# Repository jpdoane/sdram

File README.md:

# sdram

Simple Verilog controller core for the 64MB [Alliance AS4C32M16SB](docs/AS4C32M16SB.pdf) or the (pin equivalent) 32MB [Winbond W9825G6KH](docs/w9825g6kh.pdf) SDRAM modules.

Includes a [board design](board/sdram.pdf) compatible with the [ChipKit shield connector](https://digilent.com/reference/_media/reference/programmable-logic/arty-z7/arty-z7-shield.png) on the [Arty Z7-20](https://digilent.com/reference/programmable-logic/arty-z7/reference-manual)

The primary intent of this project is to support larger ROM memories for [NES fpga project](https://github.com/jpdoane/nesfpga), and that will only simple memory operations as needed by the NES core will be initially supported.

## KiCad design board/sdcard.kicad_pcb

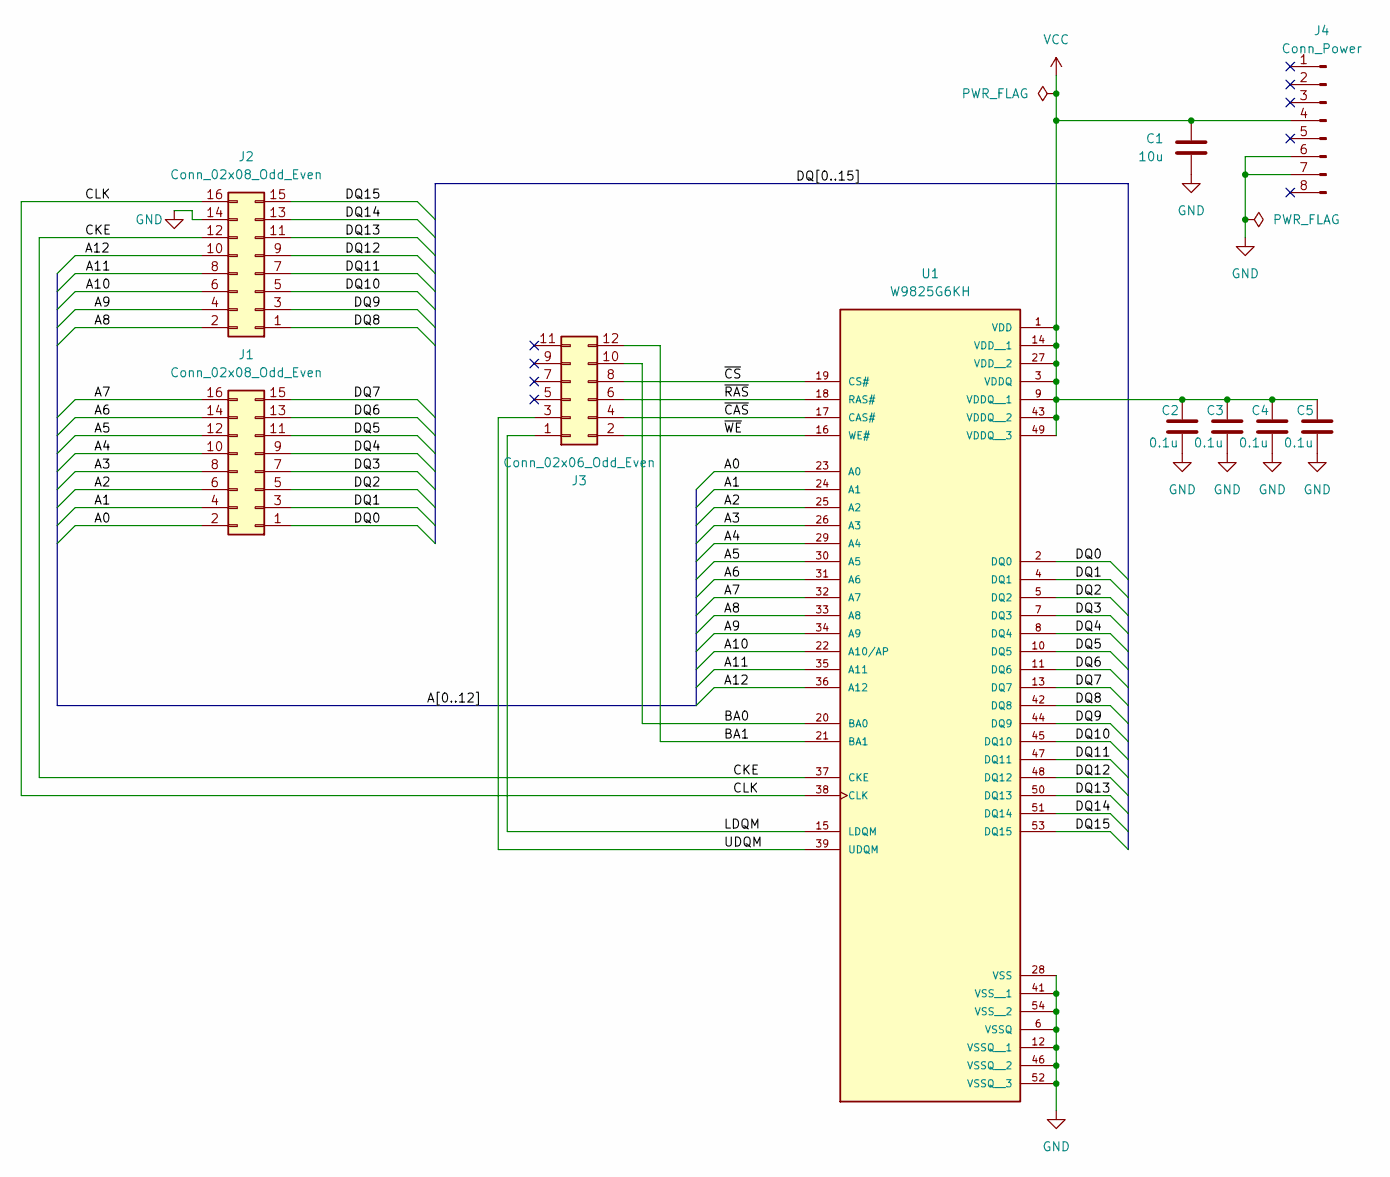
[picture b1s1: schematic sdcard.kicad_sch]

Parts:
C1: 10u; C_0805_2012Metric
C2, C3, C4, C5: 0.1u; C_0805_2012Metric
J1, J2: Conn_02x08_Odd_Even; PinHeader_2x08_P2.54mm_Vertical
J3: Conn_02x06_Odd_Even; PinHeader_2x06_P2.54mm_Vertical
J4: Conn_Power; PinHeader_1x08_P2.54mm_Vertical
U1: W9825G6KH; TSOP-II-54_22.2x10.16mm_P0.8mm; PARTREV 1.2

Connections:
/A0: J1.2, U1.23 (A0)
/A1: J1.4, U1.24 (A1)
/A2: J1.6, U1.25 (A2)
/A3: J1.8, U1.26 (A3)
/A4: J1.10, U1.29 (A4)
/A5: J1.12, U1.30 (A5)
/A6: J1.14, U1.31 (A6)
/A7: J1.16, U1.32 (A7)
/A8: J2.2, U1.33 (A8)
/A9: J2.4, U1.34 (A9)
/A10: J2.6, U1.22 (A10/AP)
/A11: J2.8, U1.35 (A11)
/A12: J2.10, U1.36 (A12)
/BA0: J3.10, U1.20 (BA0)
/BA1: J3.12, U1.21 (BA1)
/CKE: J2.12, U1.37 (CKE)
/CLK: J2.16, U1.38 (CLK)
/DQ0: J1.1, U1.2 (DQ0)
/DQ1: J1.3, U1.4 (DQ1)
/DQ2: J1.5, U1.5 (DQ2)
/DQ3: J1.7, U1.7 (DQ3)
/DQ4: J1.9, U1.8 (DQ4)
/DQ5: J1.11, U1.10 (DQ5)
/DQ6: J1.13, U1.11 (DQ6)
/DQ7: J1.15, U1.13 (DQ7)
/DQ8: J2.1, U1.42 (DQ8)
/DQ9: J2.3, U1.44 (DQ9)
/DQ10: J2.5, U1.45 (DQ10)
/DQ11: J2.7, U1.47 (DQ11)
/DQ12: J2.9, U1.48 (DQ12)
/DQ13: J2.11, U1.50 (DQ13)
/DQ14: J2.13, U1.51 (DQ14)
/DQ15: J2.15, U1.53 (DQ15)
/LDQM: J3.1, U1.15 (LDQM)
/UDQM: J3.3, U1.39 (UDQM)
/~CAS: J3.4, U1.17 (CAS#)
/~CS: J3.8, U1.19 (CS#)
/~RAS: J3.6, U1.18 (RAS#)
/~WE: J3.2, U1.16 (WE#)
GND: C1.2, C2.2, C3.2, C4.2, C5.2, J2.14, J4.6, J4.7, U1.6 (VSSQ), U1.12 (VSSQ__1), U1.28 (VSS), U1.41 (VSS__1), U1.46 (VSSQ__2), U1.52 (VSSQ__3), U1.54 (VSS__2)
VCC: C1.1, C2.1, C3.1, C4.1, C5.1, J4.4, U1.1 (VDD), U1.3 (VDDQ), U1.9 (VDDQ__1), U1.14 (VDD__1), U1.27 (VDD__2), U1.43 (VDDQ__2), U1.49 (VDDQ__3)

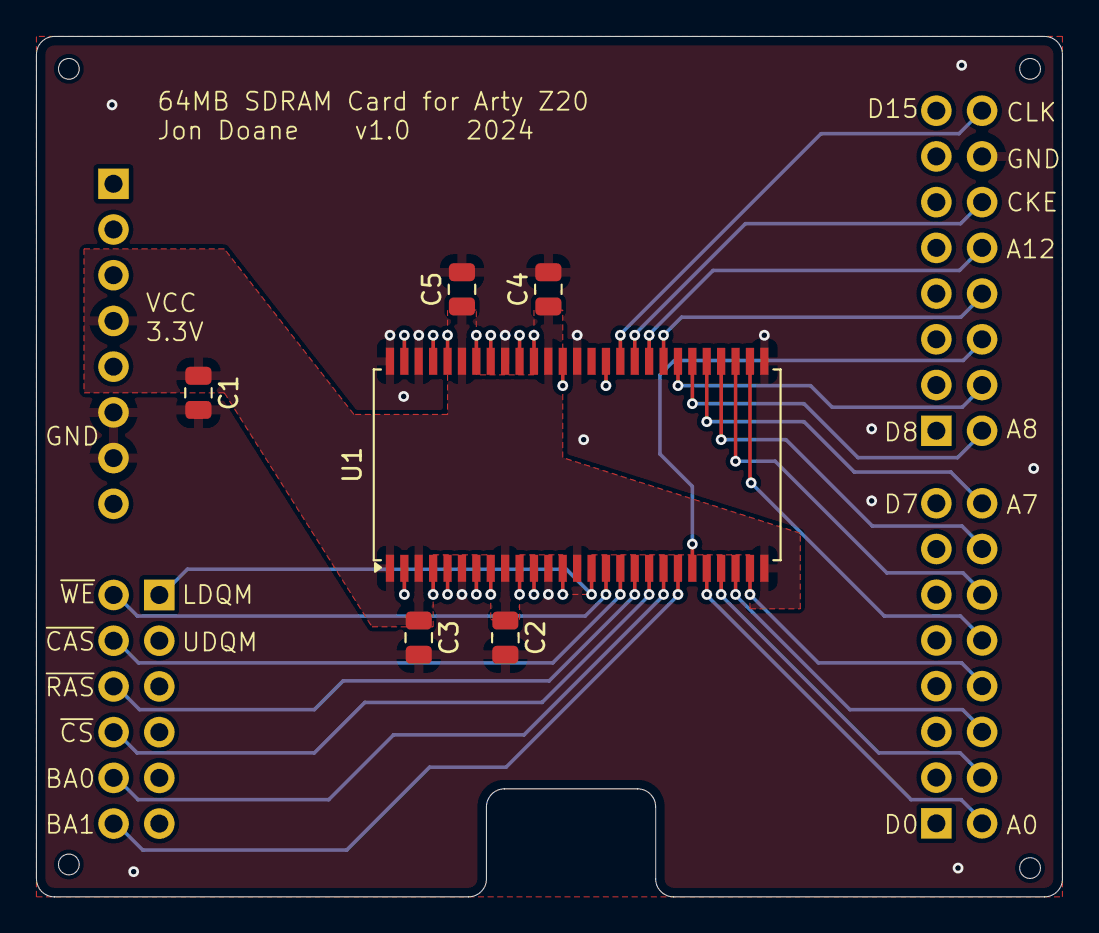
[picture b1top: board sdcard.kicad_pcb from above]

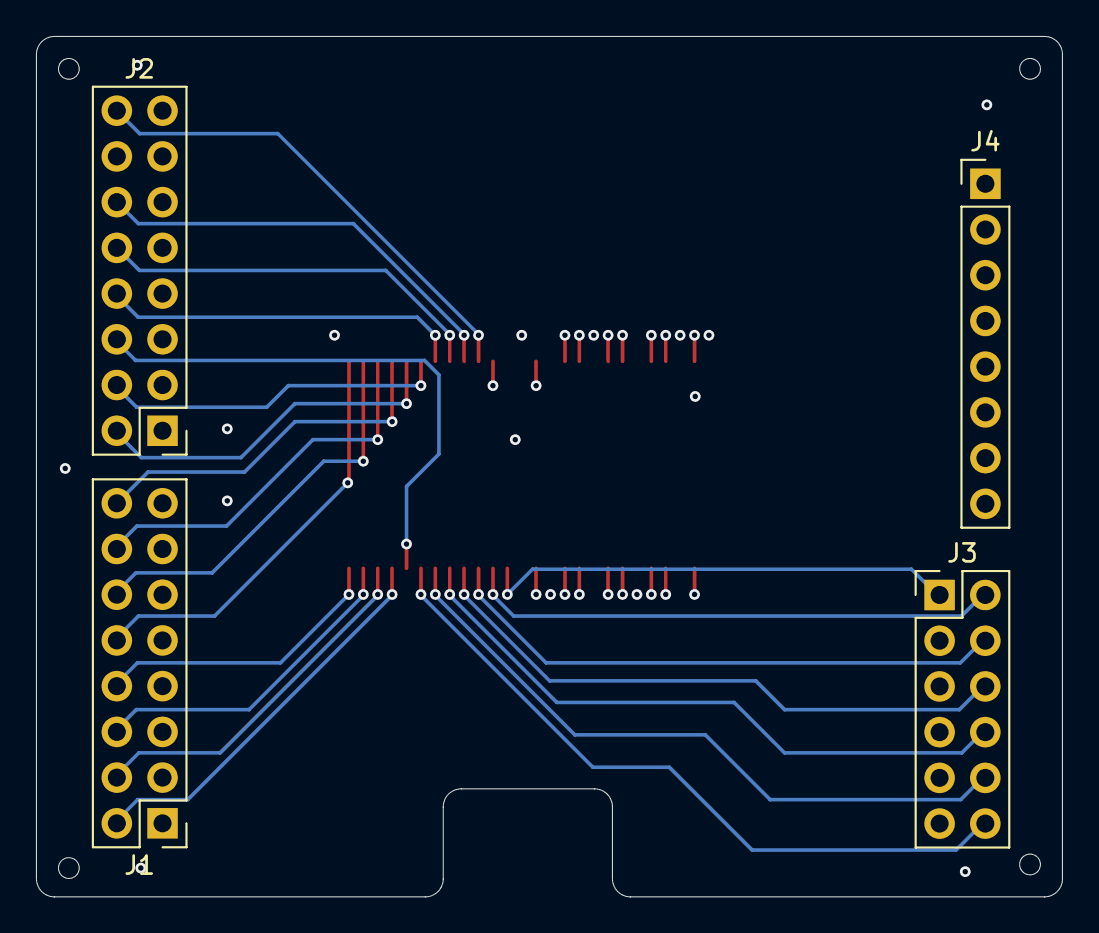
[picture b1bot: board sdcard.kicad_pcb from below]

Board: 4 copper layers, 57.0 x 47.8 mm, 10 parts (4 on the bottom side), 41 nets.

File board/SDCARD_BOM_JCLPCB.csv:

Comment,Designator,Footprint,JLCPCB Part #（optional）,Mfr Part #
SDRAM 256Mb SDR SDRAM x16,U1,TSOP-54-10.2mm ,C62246,W9825G6KH-5
10uF MLCC,C1,0805,C15850,CL21A106KAYNNNE
100nF MLCC,"C2,C3,C4,C5",0805,C28233,CL21B104KCFNNNE
2x8 pin header 2.54mm,"J1,J2","Plugin,P=2.54mm",C124389,B-2100S16P-B110 
2x6 pin header 2.54mm,J3,"Plugin,P=2.54mm",C124388,B-2100S12P-B110
1x8 pin header 2.54mm,J4,"Plugin,P=2.54mm",C124381,B-2100S08P-A110

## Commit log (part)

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2024-03-14 add board files
2024-04-14 working simple sdram controller and testbench
2024-04-16 controller for ppu and cpu access, each controlling one bank
2024-04-23 working nes memory controller with simple testbench
2024-04-23 use gated clocks in nes TB like real system
2024-04-27 I think there is a conflict for read followed by write...
2024-04-28 dual bank interface seems to work
2025-04-24 add core from Ultra-embedded which supports 32b (2x) bursts
2025-04-27 eworking sim
2025-04-27 defined core using interfaces. realized iverilog doesnt support. should I Fix sdram model to work with verilator?
2025-04-27 verilator compiles but test fails (race conditions?)
2025-04-27 I think I fixed the model so it workes with verilator
2025-04-28 working dual port
2025-04-28 updated arb module to reduce latency. currently broken
2025-05-03 theres a deadlock...
2025-05-04 clean up old core with intrefaces, rename as sdram_core.sv
2025-05-05 multi width interface seems to work, supporting 8, 16, and 32 bit datawidths
2025-05-05 confirmed byte select on write works..
2025-05-10 ignore vcd files
2025-05-10 replace ack/accept with rdy/valid, to make axi integration easier. Simplyfy core state machine
2025-05-10 rename interfaces as sdram_ctrl_if and sdram_dev_if
2025-05-10 add simple axi-lite interface
2025-05-11 working axi-lite TB
2025-05-11 cleanup directories
2025-05-11 remove clocks from interfaces
2025-05-13 remove obj_Dir
2025-05-13 fix read timing
2025-05-15 disable if tasks due multidriver errors
2025-05-18 WIP for arb module
2025-05-18 WIP arb. figuring out veriloatro interface issue with combinatoric loops
2025-05-18 working dual port mem interface works. Had to give up on interface tasks due to Verilator Bug #5116
2025-06-15 reorg and add hardware example for zynq (compiles but untested)
2025-06-17 builds but doesnt work
2025-06-21 add both controllers in parallel
2025-06-27 working single bank - getting errors for multibank
2025-06-30 update timings
2025-07-06 working - not quite sure what I did though...
2025-07-09 working on timing
2025-07-12 fixed typo in top portlest (sdram_ba). Seems to work now
2025-07-13 Working design with tests passing in sim and on hardware
2025-09-18 better verilator sim to support CPU intergraion
2025-09-18 clean up sim dir
2025-09-19 general vsim.h template for verilog models. remove and ignore sim/build
2026-05-25 dual master with axi and syncronous ports
2026-06-21 dual master controller with testbench
2026-06-22 add HIL testing
2026-06-23 python xsct wrapper. Remove old sim/ folder
2026-06-30 integrate with new zynq_tools repo. Debug still doesnt work
